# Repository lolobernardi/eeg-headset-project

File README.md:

# eeg-headset-project
Proyecto para el desarrollo de un casco EEG inalámbrico y portátil

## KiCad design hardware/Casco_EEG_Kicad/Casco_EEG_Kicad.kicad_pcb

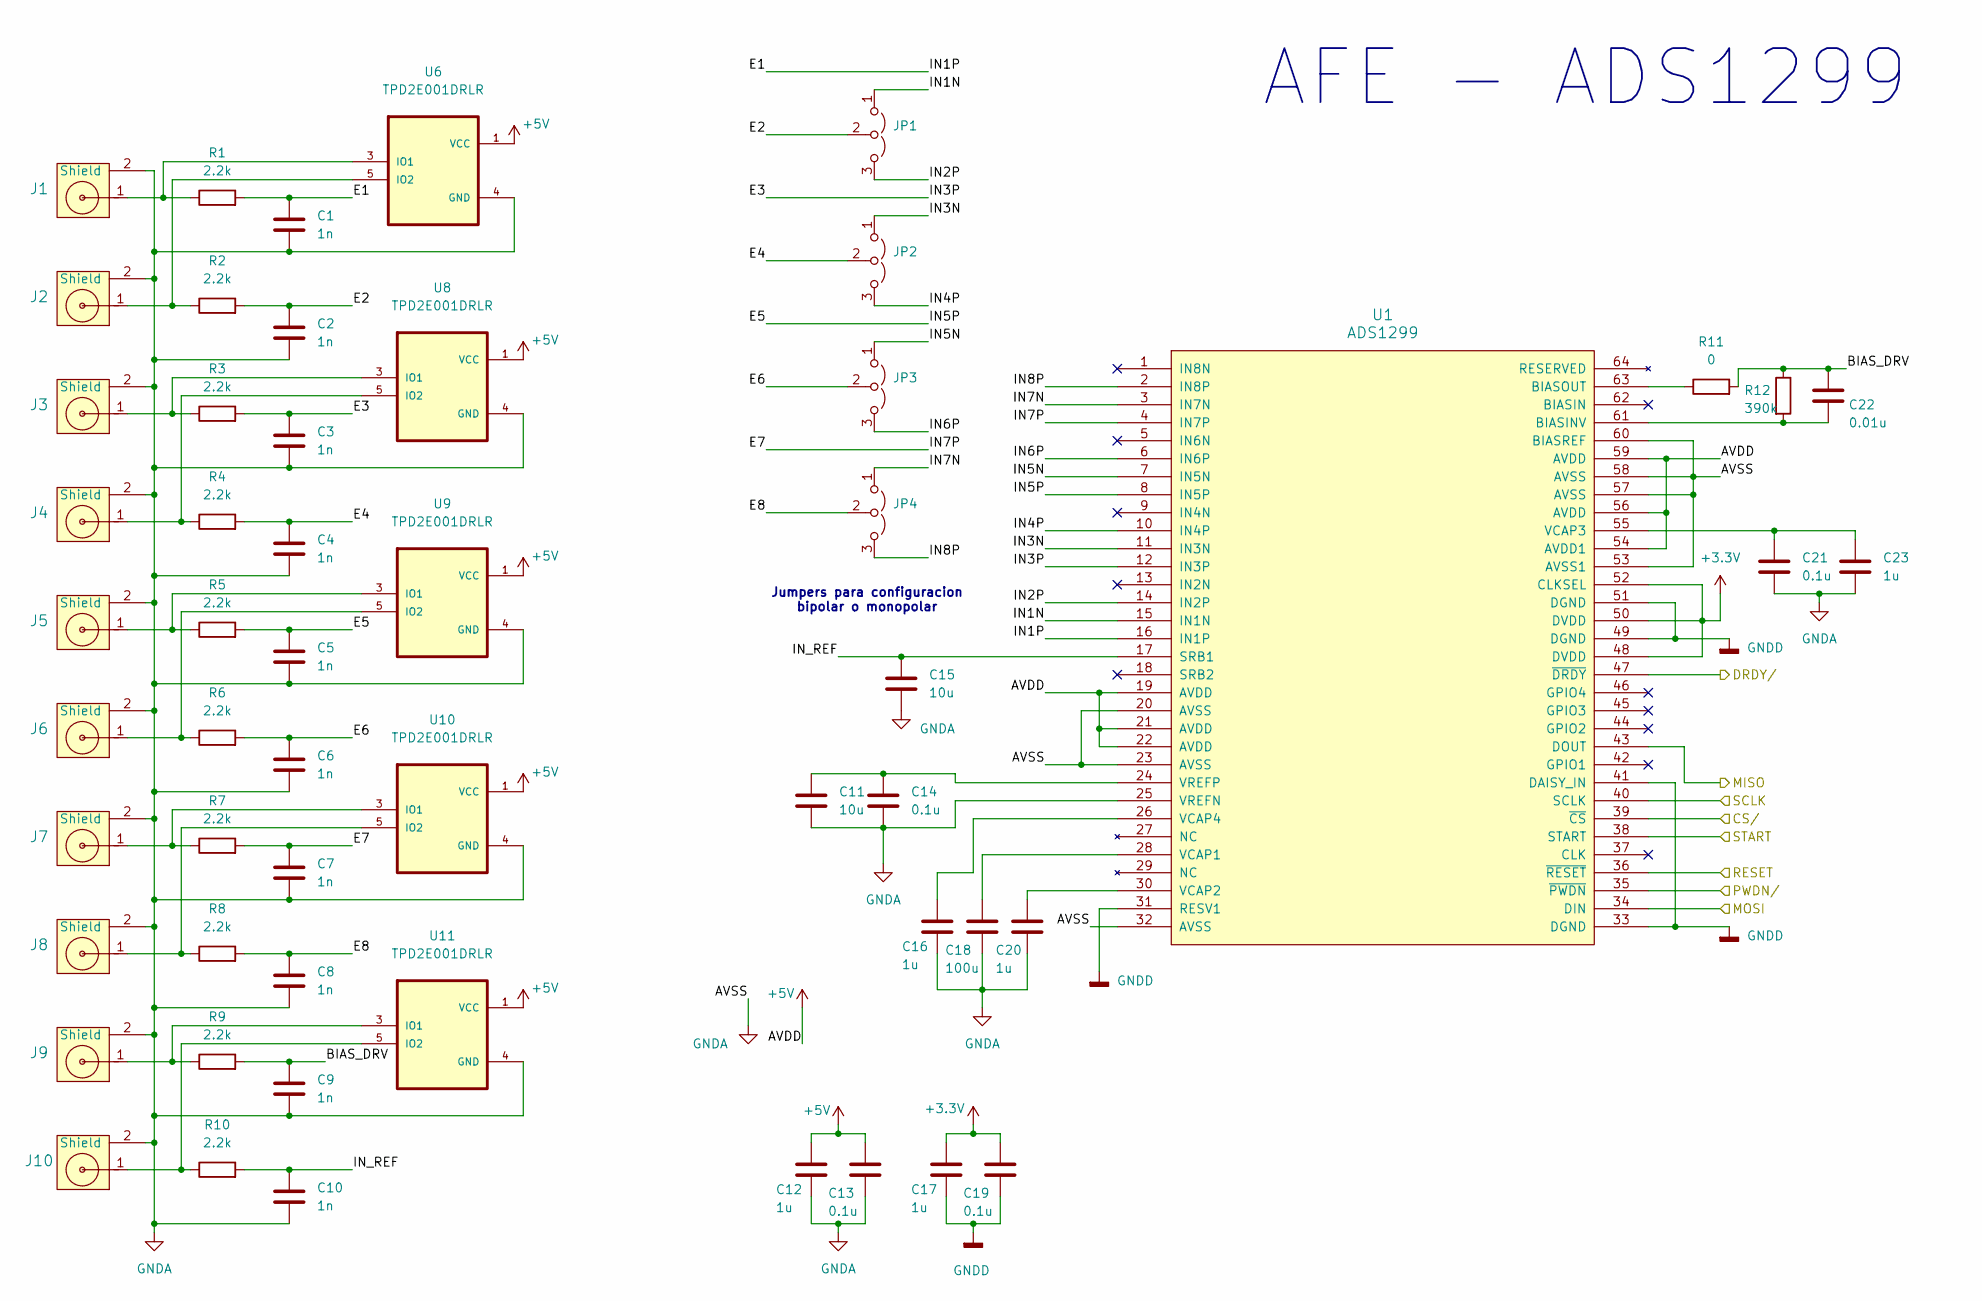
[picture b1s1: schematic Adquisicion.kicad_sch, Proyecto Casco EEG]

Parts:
C1, C2, C3, C4, C5, C6, C7, C8, C9, C10: 1n; C_0603_1608Metric; LCSC PN C1588
C11, C15: 10u; C_0603_1608Metric; LCSC PN C19702
C12, C16, C17, C20, C23: 1u; C_0603_1608Metric; LCSC PN C15849
C13, C14, C19, C21: 0.1u; C_0603_1608Metric; LCSC PN C14663
C18: 100u; C_0805_2012Metric; LCSC PN C141660
C22: 0.01u; C_0603_1608Metric; LCSC PN C57112
J1, J2, J3, J4, J5, J6, J7, J8, J9, J10: Jack_Touch-Proof; Jack_TouchProof_1.5mm
JP1, JP2, JP3, JP4: Jumper_3_Open; PinHeader_1x03_P2.54mm_Vertical
R1, R2, R3, R4, R5, R6, R7, R8, R9, R10: 2.2k; R_0603_1608Metric; LCSC PN C4190
R11: 0; R_0603_1608Metric
R12: 390k; R_0603_1608Metric; LCSC PN C23150
U1: ADS1299; PAG64_TEX; LCSC PN C476817
U6, U8, U9, U10, U11: TPD2E001DRLR; SOT50P160X60-5N; LCSC PN C150526

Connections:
+3.3V: C17.1, C19.1, U1.48 (DVDD), U1.50 (DVDD), U1.52 (CLKSEL); also elsewhere on the board
+5V: C12.1, C13.1, U1.19 (AVDD), U1.21 (AVDD), U1.22 (AVDD), U1.54 (AVDD1), U1.56 (AVDD), U1.59 (AVDD), U6.1 (VCC), U8.1 (VCC), U9.1 (VCC), U10.1 (VCC), U11.1 (VCC); also elsewhere on the board
/Adquisicion/BIAS_DRV: C9.1, C22.1, R9.2, R11.2, R12.1
/Adquisicion/CS/: U1.39 (~CS); also elsewhere on the board
/Adquisicion/DRDY/: U1.47 (~DRDY); also elsewhere on the board
/Adquisicion/E1: C1.1, R1.2, U1.16 (IN1P)
/Adquisicion/E2: C2.1, JP1.2 (C), R2.2
/Adquisicion/E3: C3.1, R3.2, U1.12 (IN3P)
/Adquisicion/E4: C4.1, JP2.2 (C), R4.2
/Adquisicion/E5: C5.1, R5.2, U1.8 (IN5P)
/Adquisicion/E6: C6.1, JP3.2 (C), R6.2
/Adquisicion/E7: C7.1, R7.2, U1.4 (IN7P)
/Adquisicion/E8: C8.1, JP4.2 (C), R8.2
/Adquisicion/IN1N: JP1.1 (A), U1.15 (IN1N)
/Adquisicion/IN2P: JP1.3 (B), U1.14 (IN2P)
/Adquisicion/IN3N: JP2.1 (A), U1.11 (IN3N)
/Adquisicion/IN4P: JP2.3 (B), U1.10 (IN4P)
/Adquisicion/IN5N: JP3.1 (A), U1.7 (IN5N)
/Adquisicion/IN6P: JP3.3 (B), U1.6 (IN6P)
/Adquisicion/IN7N: JP4.1 (A), U1.3 (IN7N)
/Adquisicion/IN8P: JP4.3 (B), U1.2 (IN8P)
/Adquisicion/IN_REF: C10.1, C15.1, R10.2, U1.17 (SRB1)
/Adquisicion/PWDN/: U1.35 (~PWDN); also elsewhere on the board
/Adquisicion/RESET: U1.36 (~RESET); also elsewhere on the board
/Adquisicion/SCLK: U1.40 (SCLK); also elsewhere on the board
/Adquisicion/START: U1.38 (START); also elsewhere on the board
/CPU/MISO: U1.43 (DOUT); also elsewhere on the board
/CPU/MOSI: U1.34 (DIN); also elsewhere on the board
GNDA: C1.2, C2.2, C3.2, C4.2, C5.2, C6.2, C7.2, C8.2, C9.2, C10.2, C11.2, C12.2, C13.2, C14.2, C15.2, C16.2, C18.2, C20.2, C21.2, C23.2, J1.2 (Shield), J2.2 (Shield), J3.2 (Shield), J4.2 (Shield), J5.2 (Shield), J6.2 (Shield), J7.2 (Shield), J8.2 (Shield), J9.2 (Shield), J10.2 (Shield), U1.20 (AVSS), U1.23 (AVSS), U1.25 (VREFN), U1.32 (AVSS), U1.53 (AVSS1), U1.57 (AVSS), U1.58 (AVSS), U1.60 (BIASREF), U6.4 (GND), U8.4 (GND), U9.4 (GND), U10.4 (GND), U11.4 (GND); also elsewhere on the board
GNDD: C17.2, C19.2, U1.31 (RESV1), U1.33 (DGND), U1.41 (DAISY_IN), U1.49 (DGND), U1.51 (DGND); also elsewhere on the board
unnamed: C22.2, R12.2, U1.61 (BIASINV)
unnamed: R11.1, U1.63 (BIASOUT)
unnamed: C18.1, U1.28 (VCAP1)
unnamed: C20.1, U1.30 (VCAP2)
unnamed: C21.1, C23.1, U1.55 (VCAP3)
unnamed: C16.1, U1.26 (VCAP4)
unnamed: C11.1, C14.1, U1.24 (VREFP)
unnamed: J1.1, R1.1, U6.3 (IO1)
unnamed: J2.1, R2.1, U6.5 (IO2)
unnamed: J3.1, R3.1, U8.3 (IO1)
unnamed: J4.1, R4.1, U8.5 (IO2)
unnamed: J5.1, R5.1, U9.3 (IO1)
unnamed: J6.1, R6.1, U9.5 (IO2)
unnamed: J7.1, R7.1, U10.3 (IO1)
unnamed: J8.1, R8.1, U10.5 (IO2)
unnamed: J9.1, R9.1, U11.3 (IO1)
unnamed: J10.1, R10.1, U11.5 (IO2)

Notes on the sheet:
AFE - ADS1299
Jumpers para configuracion bipolar o monopolar

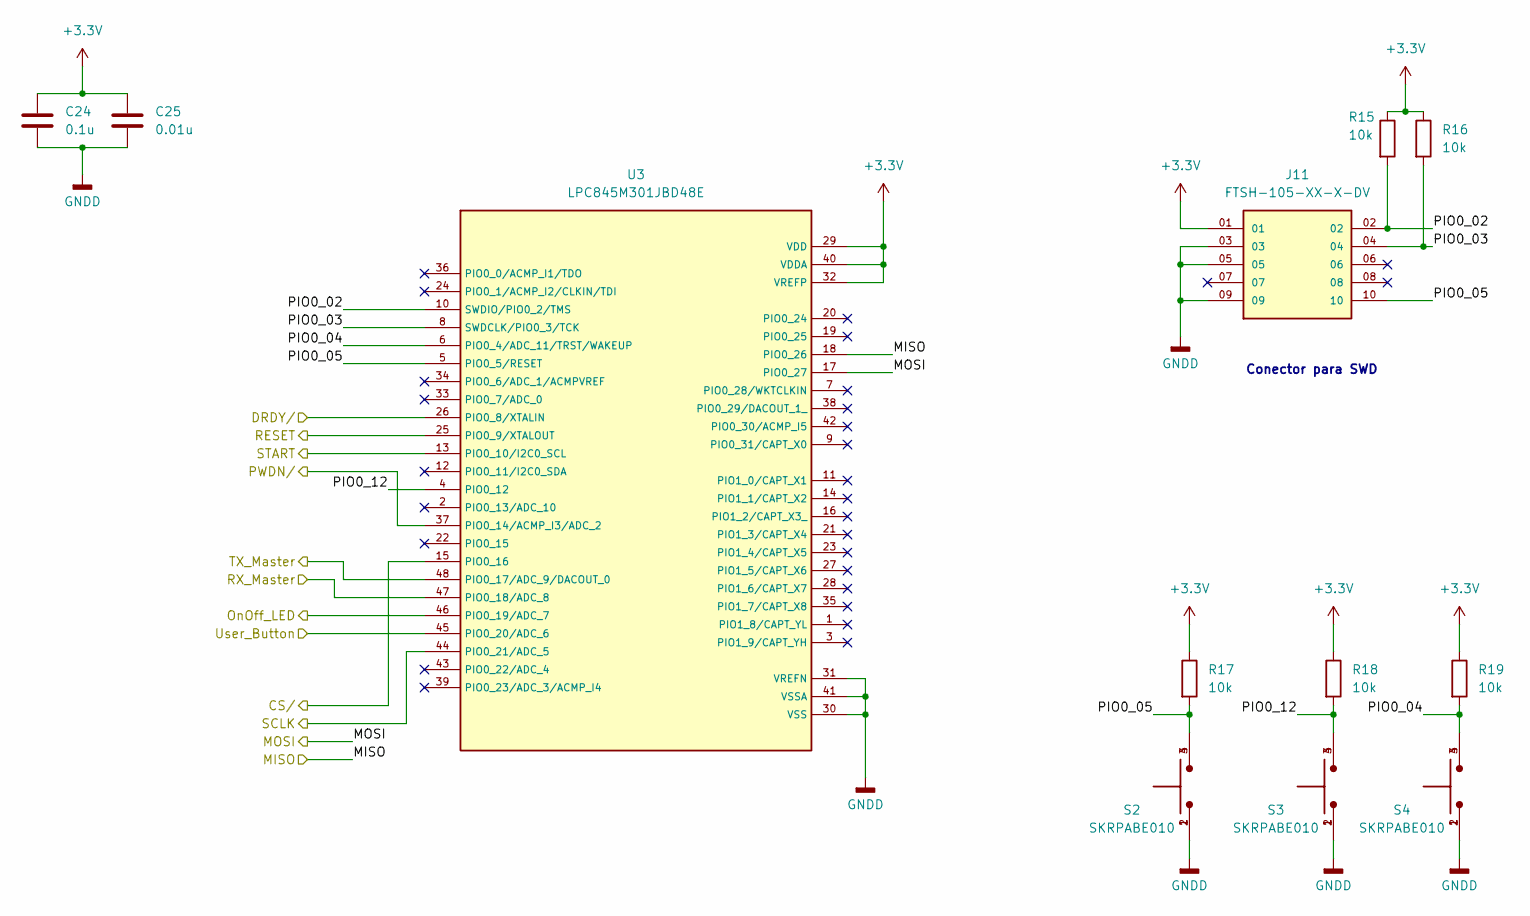
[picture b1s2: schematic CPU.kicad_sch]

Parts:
C24: 0.1u; C_0603_1608Metric; LCSC PN C14663
C25: 0.01u; C_0603_1608Metric; LCSC PN C57112
J11: FTSH-105-XX-X-DV; SAMTEC_FTSH-105-XX-X-DV; PARTREV H; LCSC PN C448647
R15, R16, R17, R18, R19: 10k; R_0603_1608Metric; LCSC PN C25804
S2, S3, S4: SKRPABE010; SW_SKRPABE010; LCSC PN C115360
U3: LPC845M301JBD48E; QFP50P900X900X160-48N; LCSC PN C178288

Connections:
+3.3V: C24.1, C25.1, J11.01, R15.1, R16.1, R17.1, R18.1, R19.1, U3.29 (VDD), U3.32 (VREFP), U3.40 (VDDA); also elsewhere on the board
/Adquisicion/CS/: U3.15 (PIO0_16); also elsewhere on the board
/Adquisicion/DRDY/: U3.26 (PIO0_8/XTALIN); also elsewhere on the board
/Adquisicion/PWDN/: U3.37 (PIO0_14/ACMP_I3/ADC_2); also elsewhere on the board
/Adquisicion/RESET: U3.25 (PIO0_9/XTALOUT); also elsewhere on the board
/Adquisicion/SCLK: U3.44 (PIO0_21/ADC_5); also elsewhere on the board
/Adquisicion/START: U3.13 (PIO0_10/I2C0_SCL); also elsewhere on the board
/CPU/MISO: U3.18 (PIO0_26); also elsewhere on the board
/CPU/MOSI: U3.17 (PIO0_27); also elsewhere on the board
/CPU/OnOff_LED: U3.46 (PIO0_19/ADC_7); also elsewhere on the board
/CPU/PIO0_02: J11.02, R15.2, U3.10 (SWDIO/PIO0_2/TMS)
/CPU/PIO0_03: J11.04, R16.2, U3.8 (SWDCLK/PIO0_3/TCK)
/CPU/PIO0_04: R19.2, S4.3, S4.4, U3.6 (PIO0_4/ADC_11/TRST/WAKEUP)
/CPU/PIO0_05: J11.10, R17.2, S2.3, S2.4, U3.5 (PIO0_5/RESET)
/CPU/PIO0_12: R18.2, S3.3, S3.4, U3.4 (PIO0_12)
/CPU/RX_Master: U3.47 (PIO0_18/ADC_8); also elsewhere on the board
/CPU/TX_Master: U3.48 (PIO0_17/ADC_9/DACOUT_0); also elsewhere on the board
/CPU/User_Button: U3.45 (PIO0_20/ADC_6); also elsewhere on the board
GNDD: C24.2, C25.2, J11.03, J11.05, J11.09, S2.1, S2.2, S3.1, S3.2, S4.1, S4.2, U3.30 (VSS), U3.31 (VREFN), U3.41 (VSSA); also elsewhere on the board

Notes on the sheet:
Conector para SWD

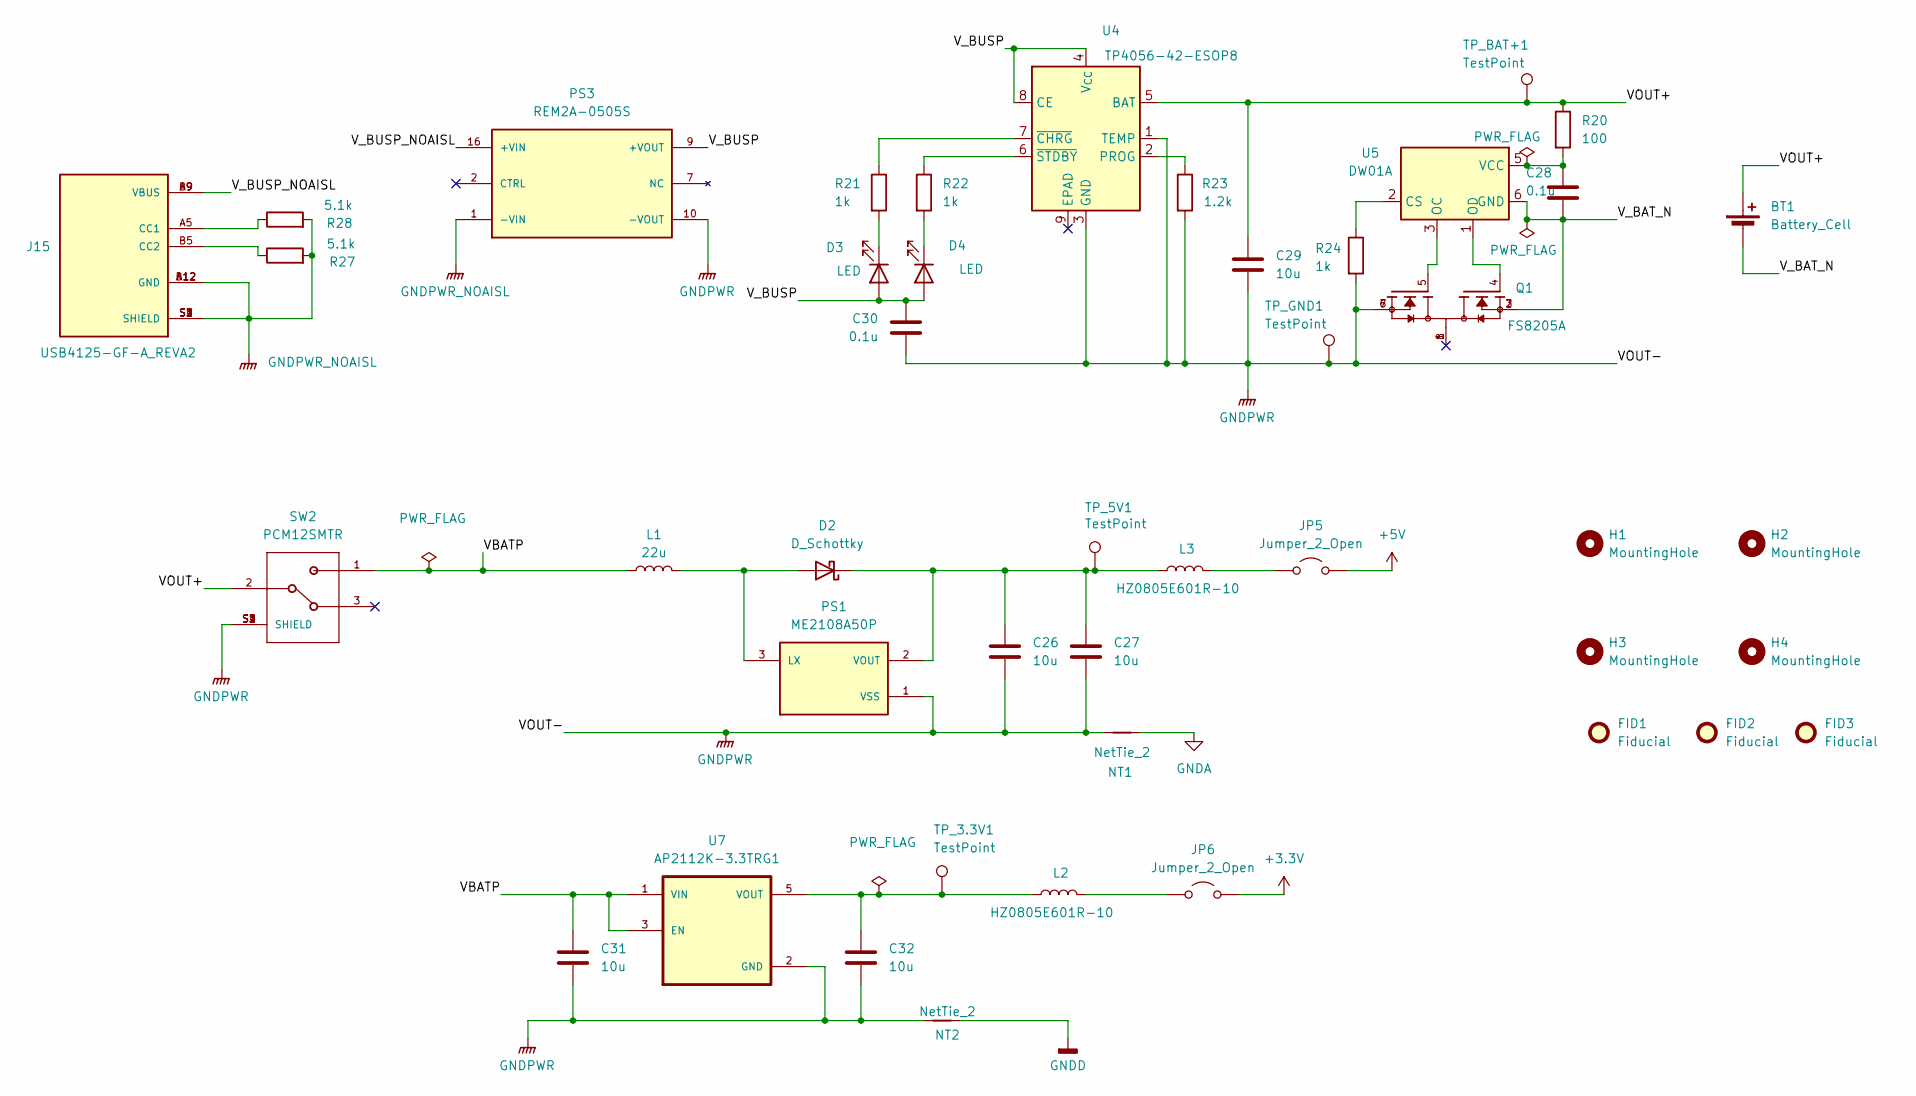
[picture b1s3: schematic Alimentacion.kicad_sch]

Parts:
BT1: Battery_Cell; BatteryHolder_Keystone_1042_1x18650
C26, C27: 10u; C_0805_2012Metric; LCSC PN C19702
C28, C30: 0.1u; C_0603_1608Metric; LCSC PN C14663
C29, C31, C32: 10u; C_0603_1608Metric; LCSC PN C19702
D2: D_Schottky; D_SMA; LCSC PN C2480
D3, D4: LED; LED_0603_1608Metric
FID1, FID2, FID3: Fiducial; Fiducial_0.5mm_Mask1mm
H1, H2, H3, H4: MountingHole; MountingHole_2.2mm_M2_Pad_Via
J15: USB4125-GF-A_REVA2; GCT_USB4125-GF-A_REVA2; PARTREV Rev A2
JP5, JP6: Jumper_2_Open; SolderJumper-2_P1.3mm_Open_RoundedPad1.0x1.5mm
L1: 22u; L_Coilcraft_XAL5030-XXX
L2, L3: HZ0805E601R-10; L_Eaton_MCL2012V1; LCSC PN C2441364
NT1, NT2: NetTie_2; NetTie-2_SMD_Pad2.0mm
PS1: ME2108A50P; CONV_ME2108A33P; LCSC PN C236798
PS3: REM2A-0505S; CONV_REM2A-0505S; PARTREV PRELIMINARY
Q1: FS8205A; SOP65P640X120-8N; PARTREV 1.7; LCSC PN C2830320
R20: 100; R_0603_1608Metric; LCSC PN C22775
R21, R22, R24: 1k; R_0603_1608Metric; LCSC PN C21190
R23: 1.2k; R_0603_1608Metric; LCSC PN C22765
R27, R28: 5.1k; R_0603_1608Metric; LCSC PN C23186
SW2: PCM12SMTR; SW_PCM12SMTR
TP_3.3V1, TP_5V1: TestPoint; TestPoint_Pad_D2.0mm
TP_BAT+1: TestPoint; TestPoint_Pad_D2.0mm
TP_GND1: TestPoint; TestPoint_Pad_D2.0mm
U4: TP4056-42-ESOP8; SOIC-8-1EP_3.9x4.9mm_P1.27mm_EP2.41x3.3mm_ThermalVias; LCSC PN C16581
U5: DW01A; SOT-23-6; LCSC PN C2927799
U7: AP2112K-3.3TRG1; SOT95P285X140-5N; PARTREV 2-2; LCSC PN C51118

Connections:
+3.3V: JP6.2 (B); also elsewhere on the board
+5V: JP5.2 (B); also elsewhere on the board
/Alimentacion/VBATP: C31.1, L1.1, SW2.1, U7.1 (VIN), U7.3 (EN)
/Alimentacion/VOUT+: BT1.1 (+), C29.1, R20.1, SW2.2, TP_BAT+1.1, U4.5 (BAT)
/Alimentacion/V_BAT_N: BT1.2 (-), C28.2, Q1.2, Q1.3, U5.6 (GND)
/Alimentacion/V_BUSP: C30.1, D3.2 (A), D4.2 (A), PS3.9 (+VOUT), U4.4 (V_{CC}), U4.8 (CE)
/Alimentacion/V_BUSP_NOAISL: J15.A9 (VBUS), J15.B9 (VBUS), PS3.16 (+VIN)
GNDA: NT1.2; also elsewhere on the board
GNDD: NT2.2; also elsewhere on the board
GNDPWR: C26.2, C27.2, C29.2, C30.2, C31.2, C32.2, NT1.1, NT2.1, PS1.1 (VSS), PS3.10 (-VOUT), Q1.6, Q1.7, R23.2, R24.2, SW2.S1 (SHIELD), SW2.S2 (SHIELD), SW2.S3 (SHIELD), SW2.S4 (SHIELD), TP_GND1.1, U4.1 (TEMP), U4.3 (GND), U7.2 (GND)
GNDPWR_NOAISL: J15.A12 (GND), J15.B12 (GND), J15.S1 (SHIELD), J15.S2 (SHIELD), J15.S3 (SHIELD), J15.S4 (SHIELD), PS3.1 (-VIN), R27.2, R28.2
unnamed: D2.2 (A), L1.2, PS1.3 (LX)
unnamed: C26.1, C27.1, D2.1 (K), L3.1, PS1.2 (VOUT), TP_5V1.1
unnamed: D3.1 (K), R21.2
unnamed: D4.1 (K), R22.2
unnamed: J15.A5 (CC1), R28.1
unnamed: J15.B5 (CC2), R27.1
unnamed: JP5.1 (A), L3.2
unnamed: JP6.1 (A), L2.2
unnamed: R23.1, U4.2 (PROG)
unnamed: R21.1, U4.7 (~CHRG)
unnamed: R22.1, U4.6 (~STDBY)
unnamed: R24.1, U5.2 (CS)
unnamed: Q1.5, U5.3 (OC)
unnamed: Q1.4, U5.1 (OD)
unnamed: C28.1, R20.2, U5.5 (VCC)
unnamed: C32.1, L2.1, TP_3.3V1.1, U7.5 (VOUT)

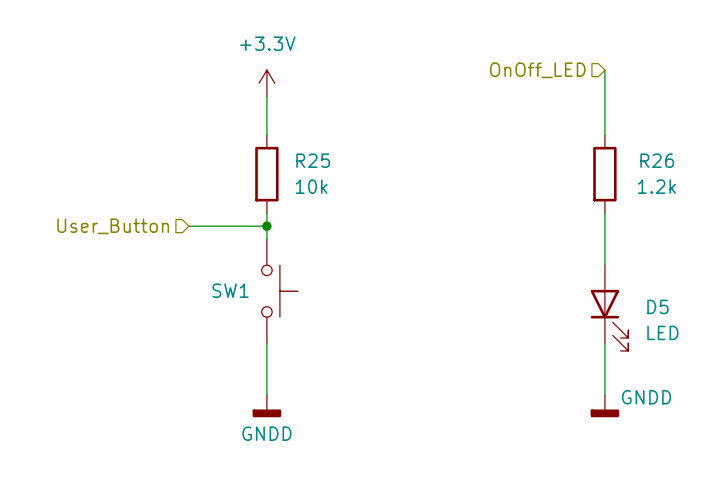
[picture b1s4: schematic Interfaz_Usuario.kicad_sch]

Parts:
D5: LED; LED_0603_1608Metric
R25: 10k; R_0603_1608Metric; LCSC PN C25804
R26: 1.2k; R_0603_1608Metric; LCSC PN C22765
SW1: SW_Push; SW_SPST_TL3305A

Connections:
+3.3V: R25.1; also elsewhere on the board
/CPU/OnOff_LED: R26.1; also elsewhere on the board
/CPU/User_Button: R25.2, SW1.1; also elsewhere on the board
GNDD: D5.1 (K), SW1.2; also elsewhere on the board
unnamed: D5.2 (A), R26.2

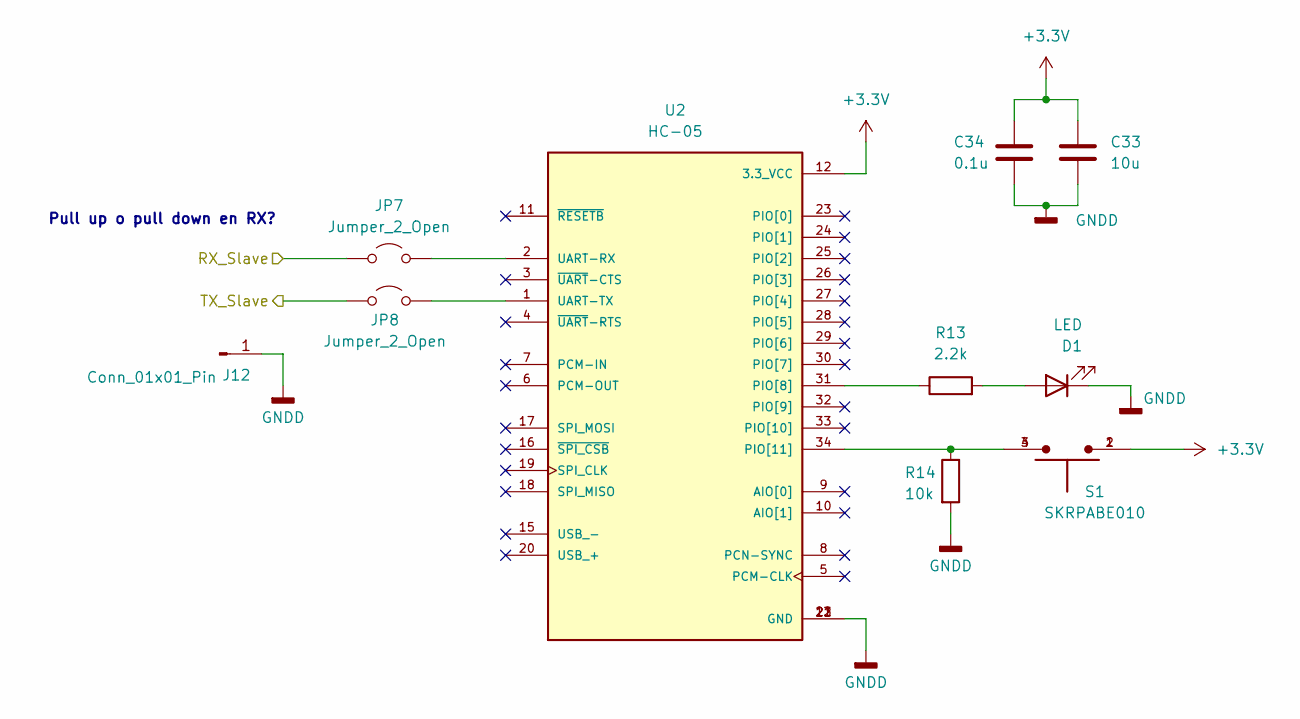
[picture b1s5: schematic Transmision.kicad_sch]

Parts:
C33: 10u; C_0603_1608Metric; LCSC PN C19702
C34: 0.1u; C_0603_1608Metric; LCSC PN C14663
D1: LED; LED_0603_1608Metric; LCSC PN C19171394
J12: Conn_01x01_Pin; PinHeader_1x01_P2.54mm_Vertical
JP7, JP8: Jumper_2_Open; PinHeader_1x02_P2.54mm_Vertical
R13: 2.2k; R_0603_1608Metric; LCSC PN C4190
R14: 10k; R_0603_1608Metric; LCSC PN C25804
S1: SKRPABE010; SW_SKRPABE010; LCSC PN C115360
U2: HC-05; XCVR_HC-05; PARTREV v1.0

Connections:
+3.3V: C33.1, C34.1, S1.1, S1.2, U2.12 (3.3_VCC); also elsewhere on the board
/CPU/RX_Master: JP8.1 (A); also elsewhere on the board
/CPU/TX_Master: JP7.1 (A); also elsewhere on the board
GNDD: C33.2, C34.2, D1.1 (K), J12.1, R14.2, U2.13 (GND), U2.21 (GND), U2.22 (GND); also elsewhere on the board
unnamed: D1.2 (A), R13.2
unnamed: JP7.2 (B), U2.2 (UART-RX)
unnamed: JP8.2 (B), U2.1 (UART-TX)
unnamed: R13.1, U2.31 (PIO[8])
unnamed: R14.1, S1.3, S1.4, U2.34 (PIO[11])

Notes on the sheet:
Pull up o pull down en RX?

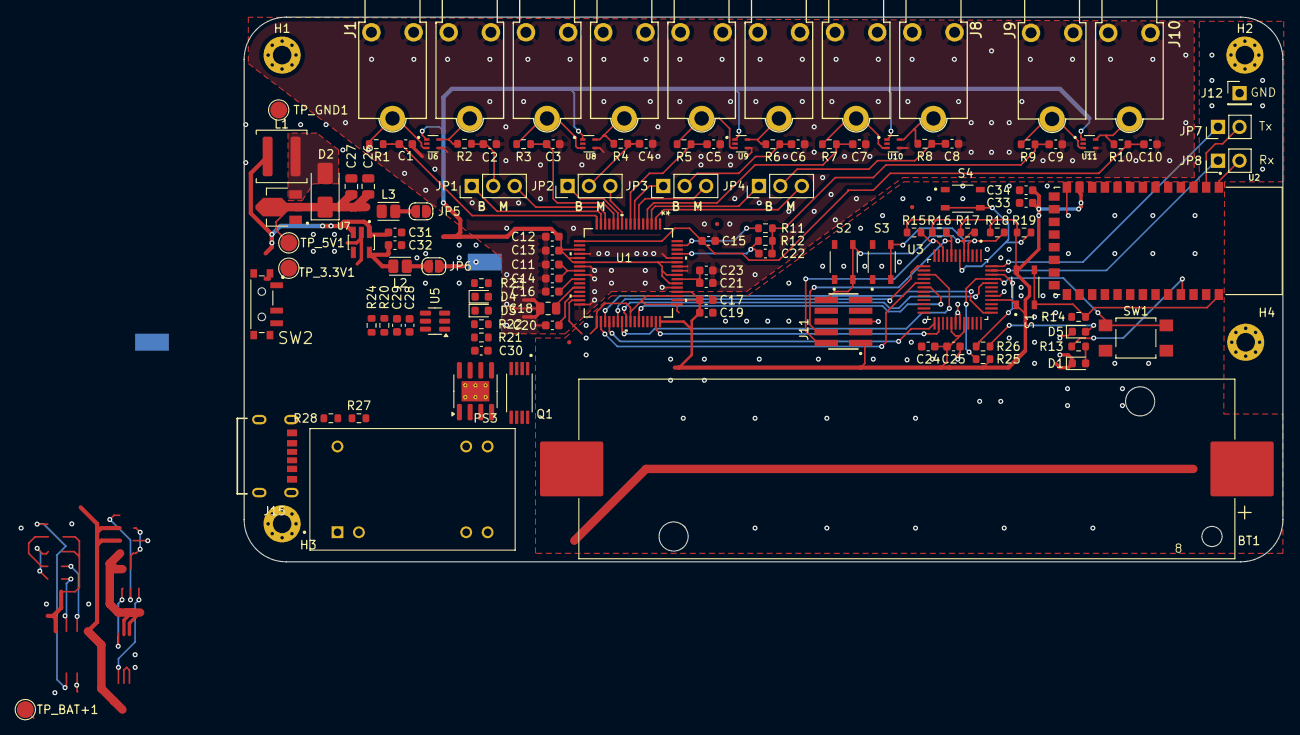
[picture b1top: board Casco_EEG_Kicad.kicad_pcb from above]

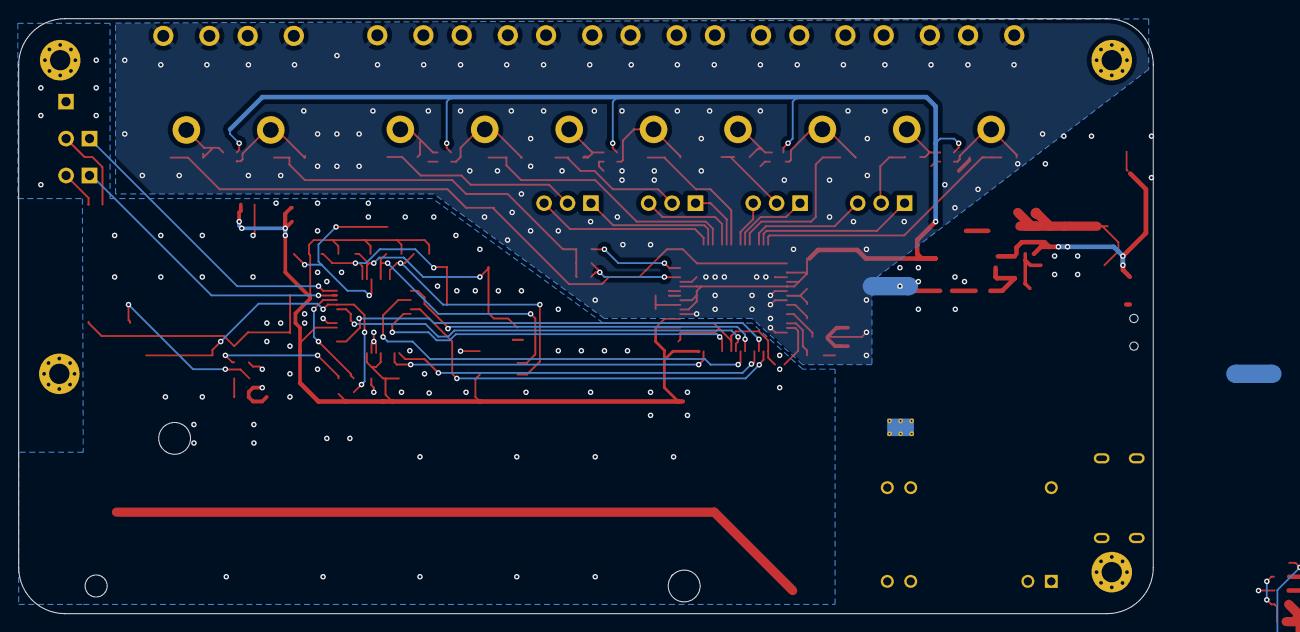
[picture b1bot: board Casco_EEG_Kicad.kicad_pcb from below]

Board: 2 copper layers, 123.0 x 64.5 mm, 125 parts (2 on the bottom side), 85 nets.

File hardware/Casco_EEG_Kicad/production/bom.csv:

Designator,Footprint,Quantity,Value,LCSC Part #
BT1,BatteryHolder_Keystone_1042_1x18650,1,Battery_Cell,
"C1, C10, C2, C3, C4, C5, C6, C7, C8, C9",0603,10,1n,C1588
"C11, C15, C29, C31, C32",0603,5,10u,C19702
"C12, C16, C17, C20, C23",0603,5,1u,C15849
"C13, C14, C19, C21, C24, C28, C30",0603,7,0.1u,C14663
C18,0805,1,100u,C141660
"C22, C25",0603,2,0.01u,C57112
"C26, C27",0805,2,10u,C19702
C33,0603,1,10u,
C34,0603,1,0.1u,
D1,0603,1,LED,C19171394
D2,D_SMA,1,D_Schottky,C2480
"D3, D4, D5",0603,3,LED,
"J1, J10, J2, J3, J4, J5, J6, J7, J8, J9",Jack_TouchProof_1.5mm,10,Jack_Touch-Proof,
J11,SAMTEC_FTSH-105-XX-X-DV,1,FTSH-105-XX-X-DV,C448647
J13,PinHeader_1x09_P2.54mm_Horizontal,1,Conn_01x09_Pin,
J15,GCT_USB4125-GF-A_REVA2,1,USB4125-GF-A_REVA2,
"JP5, JP6",SolderJumper-2_P1.3mm_Open_RoundedPad1.0x1.5mm,2,Jumper_2_Open,
"JP7, JP8",PinHeader_1x02_P2.54mm_Vertical,2,Jumper_2_Open,
L1,L_Coilcraft_XAL5030-XXX,1,22u,
"L2, L3",L_Eaton_MCL2012V1,2,HZ0805E601R-10,C2441364
PS1,CONV_ME2108A33P,1,ME2108A50P,C236798
Q1,SOP65P640X120-8N,1,FS8205A,C2830320
"R1, R10, R2, R3, R4, R5, R6, R7, R8, R9",0603,10,2.2k,C114662
R11,0603,1,0,
R12,0603,1,390k,C23150
R13,0603,1,2.2k,
"R14, R15, R16, R17, R18, R19, R25",0603,7,10k,C25804
R20,0603,1,100,C22775
"R21, R22, R24",0603,3,1k,C21190
"R23, R26",0603,2,1.2k,C22765
"R27, R28",0603,2,5.1k,C21190
"S1, S2, S3, S4",SW_SKRPABE010,4,SKRPABE010,C115360
SW1,SW_SPST_TL3305A,1,SW_Push,
SW2,SW_PCM12SMTR,1,PCM12SMTR,
"TP_3.3V1, TP_5V1, TP_BAT+1, TP_GND1",TestPoint_Pad_D2.0mm,4,TestPoint,
U1,PAG64_TEX,1,ADS1299,C476817
"U10, U11, U6, U8, U9",SOT50P160X60-5N,5,TPD2E001DRLR,C150526
U2,XCVR_HC-05,1,HC-05,
U3,QFP50P900X900X160-48N,1,LPC845M301JBD48E,C178288
U4,SOIC-8-1EP_3.9x4.9mm_P1.27mm_EP2.41x3.3mm_ThermalVias,1,TP4056-42-ESOP8,C16581
U5,SOT-23-6,1,DW01A,C2927799
U7,SOT95P285X140-5N,1,AP2112K-3.3TRG1,C51118

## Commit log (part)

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2025-05-17 Inicializacion del repositorio con estructura basica
2025-05-17 Prueba en carpeta docs
2025-05-17 Agrego .gitignore para excluir archivos del IDE y binarios
2025-05-26 Importacion de ejemplos de SDK
2025-08-05 Actualizo ejemplos del SDK
2025-08-06 Actualizacion de los archivos del SDK
2025-08-11 Creo archivos para driver de ADS1299
2025-08-11 Implement ADS1299 driver and header
2025-08-12 Add basic ADS1299 register test
2025-08-13 Se agrega funcion de test para lectura y escritura de registros en ADS
2025-08-14 Resolucion de conflicto con stash
2025-08-14 Apliacion de funciones para ADS1299
2025-08-23 Lectura y escritura de registros del ADS funcionando
2025-09-03 Transmision basica funcional de datos al GUI de OpenBCI, agrego Bluetooth driver y openBCI communication
2025-09-04 Nuevas funciones del Driver implementadas
2025-09-05 Implementacion de funciones para configurar registros de canales en ADS, sin probarfuncionamiento
2025-09-16 Agrego .gitignore para logs, IDE y binarios
2025-09-16 Implementacion de BIAS y configuracion CONFIG3, EEG funcionando
2025-09-25 Nuevo orden de carpetas y cambio de default settings
2025-09-25 Elimino ejemplos del SDK
2025-09-25 Incluyo directorio con el proyecto de KiCad
2025-10-02 Ignoro backups de Kicad, ligs, etc
2025-10-02 Primera implementacion de PCB, cambios varios
2025-10-02 Ignoro backups de Kicad, logs, etc.
2025-10-09 Nuevos cambios al PCB, mejoro planos, regulo 3,3V desde 5V, etc
2025-10-09 Implemento pines I/O para trigger
2025-10-22 Actualizacion del modelo, agrego mini slide switch, agrego jumpers para comunicacion con modulo BT
2025-10-28 Modifico pistas, cambios menores
2025-10-31 Agrego protecciones a las entradas analogicas, quito jumpers dealimentacion, agrego capacitores al HC05
2025-11-04 Cambio jumpers
2025-11-11 Agrego GND para puente UART al modulo BT
2025-12-21 Agrego configuracion para poder realizar registros monopolares, desactivo entradas negativas para la conformacion de la señal de BIAS
2025-12-21 Ignoro carpeta de produccion de hardware
2026-03-20 Actualización de pcb con aislamiento dc/dc, elimino entradas de trigger
2026-03-20 Actualizo PDF del esquematico
